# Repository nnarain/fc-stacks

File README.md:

# FC Stacks

Boards for drone electronics stacks

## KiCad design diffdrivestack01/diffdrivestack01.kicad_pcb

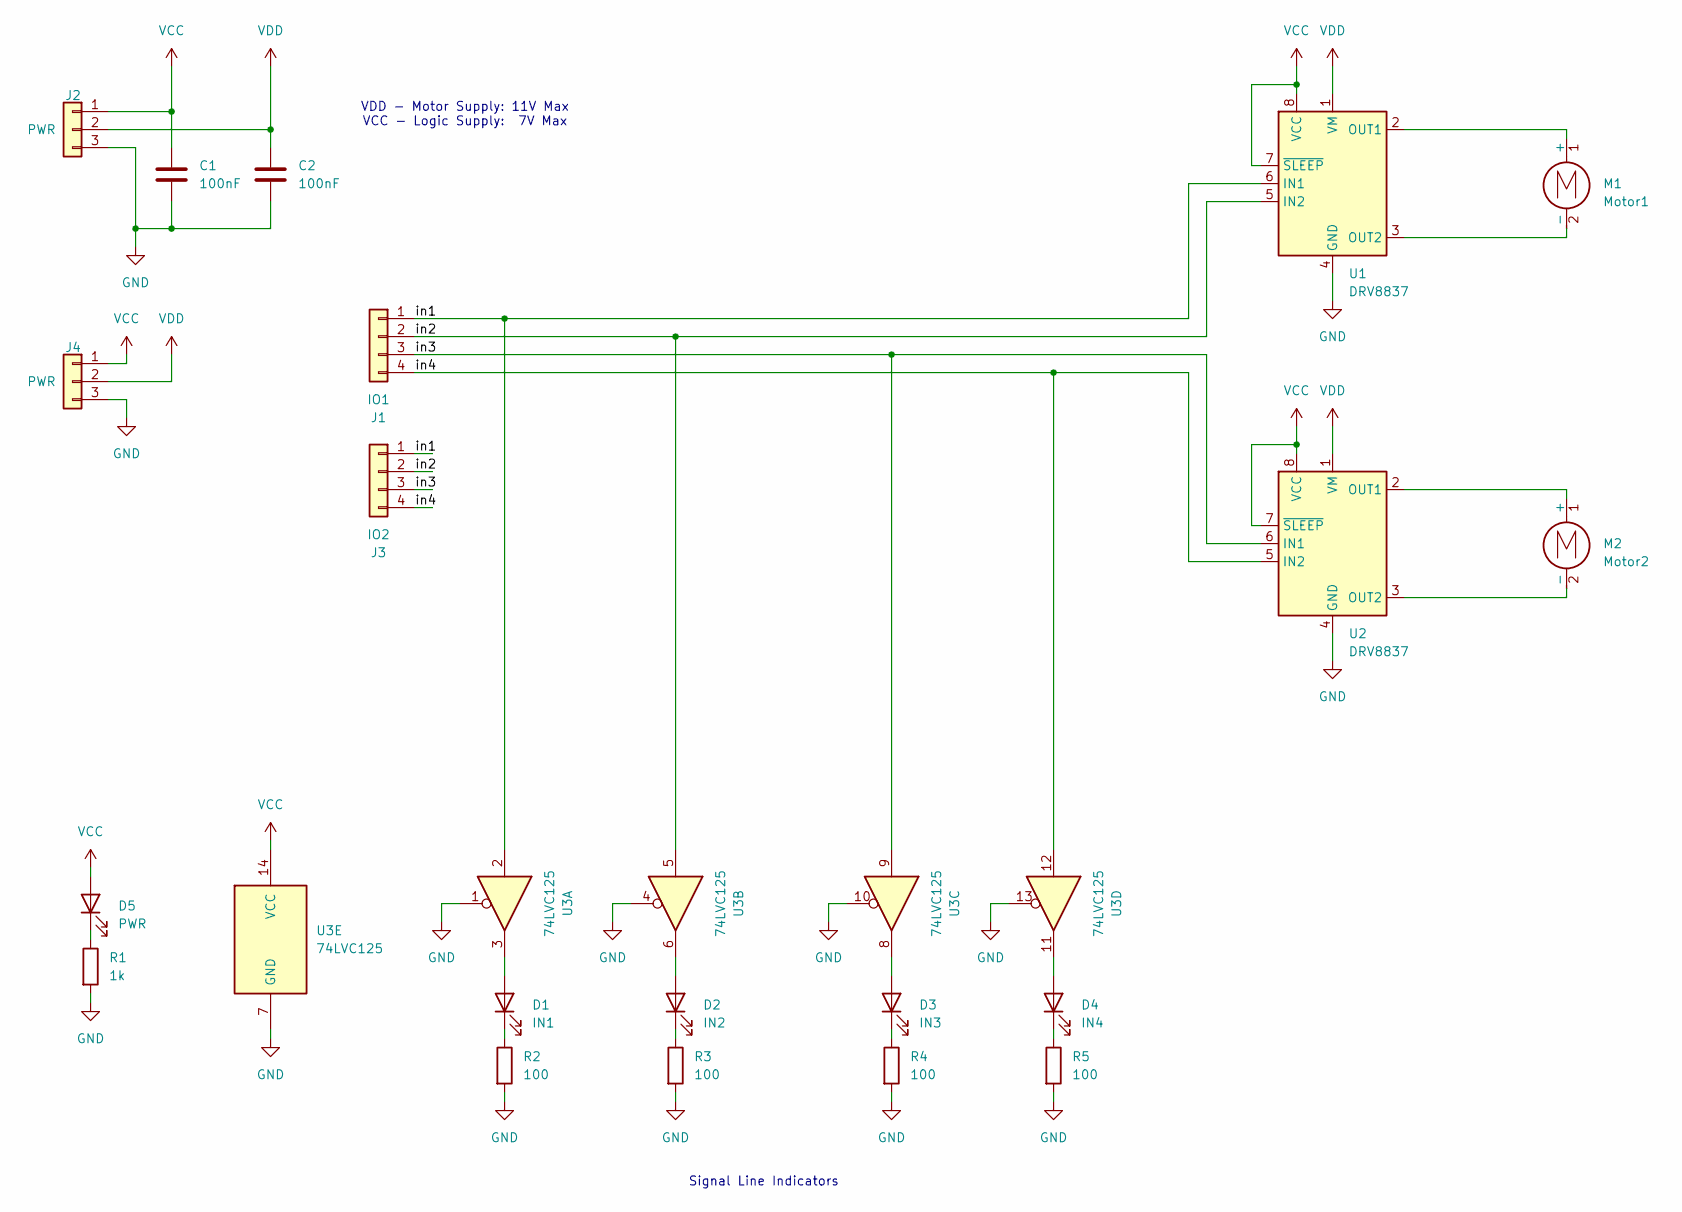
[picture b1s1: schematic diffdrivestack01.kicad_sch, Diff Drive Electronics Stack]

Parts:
C1, C2: 100nF; C_0402_1005Metric
D1: IN1; LED_0603_1608Metric; LCSC C5252984
D2: IN2; LED_0603_1608Metric; LCSC C5252984
D3: IN3; LED_0603_1608Metric; LCSC C5252984
D4: IN4; LED_0603_1608Metric; LCSC C5252984
D5: PWR; LED_0603_1608Metric; LCSC C2286
J1: IO1; SMD_4x1_1.5x1.5mm_1
J2, J4: PWR; SMD_3x1_1.5x1.5mm
J3: IO2; SMD_4x1_1.5x1.5mm_1
M1: Motor1; SMD_2x1_1.5x1.5mm
M2: Motor2; SMD_2x1_1.5x1.5mm
R1: 1k; R_0402_1005Metric; LCSC C25543
R2, R3, R4, R5: 100; R_0402_1005Metric; LCSC C25076
U1, U2: DRV8837; WSON-8-1EP_2x2mm_P0.5mm_EP0.9x1.6mm
U3: 74LVC125; TSSOP-14_4.4x5mm_P0.65mm; LCSC C6059

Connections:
/in1: J1.1, J3.1, U1.6 (IN1), U3.2
/in2: J1.2, J3.2, U1.5 (IN2), U3.5
/in3: J1.3, J3.3, U2.6 (IN1), U3.9
/in4: J1.4, J3.4, U2.5 (IN2), U3.12
GND: C1.2, C2.2, J2.3, J4.3, R1.2, R2.2, R3.2, R4.2, R5.2, U1.4 (GND), U1.9 (GND), U2.4 (GND), U2.9 (GND), U3.1, U3.4, U3.7 (GND), U3.10, U3.13
unnamed: D1.2 (A), U3.3
unnamed: D1.1 (K), R2.1
unnamed: D2.2 (A), U3.6
unnamed: D2.1 (K), R3.1
unnamed: D3.2 (A), U3.8
unnamed: D3.1 (K), R4.1
unnamed: D4.2 (A), U3.11
unnamed: D4.1 (K), R5.1
unnamed: D5.1 (K), R1.1
unnamed: M1.1 (+), U1.2 (OUT1)
unnamed: M1.2 (-), U1.3 (OUT2)
unnamed: M2.1 (+), U2.2 (OUT1)
unnamed: M2.2 (-), U2.3 (OUT2)
VCC: C1.1, D5.2 (A), J2.1, J4.1, U1.7 (~SLEEP), U1.8 (VCC), U2.7 (~SLEEP), U2.8 (VCC), U3.14 (VCC)
VDD: C2.1, J2.2, J4.2, U1.1 (VM), U2.1 (VM)

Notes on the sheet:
VDD - Motor Supply: 11V Max VCC - Logic Supply: 7V Max
Signal Line Indicators

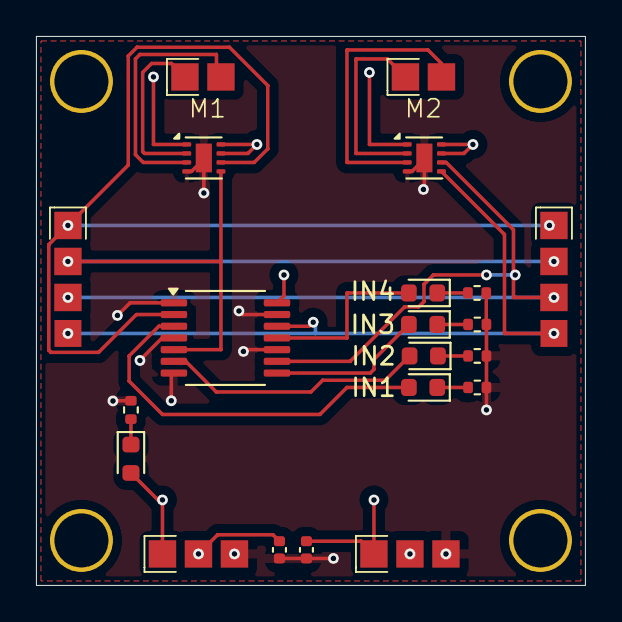
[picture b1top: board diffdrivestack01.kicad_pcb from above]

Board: 4 copper layers, 30.5 x 30.5 mm, 21 parts (0 on the bottom side), 20 nets.

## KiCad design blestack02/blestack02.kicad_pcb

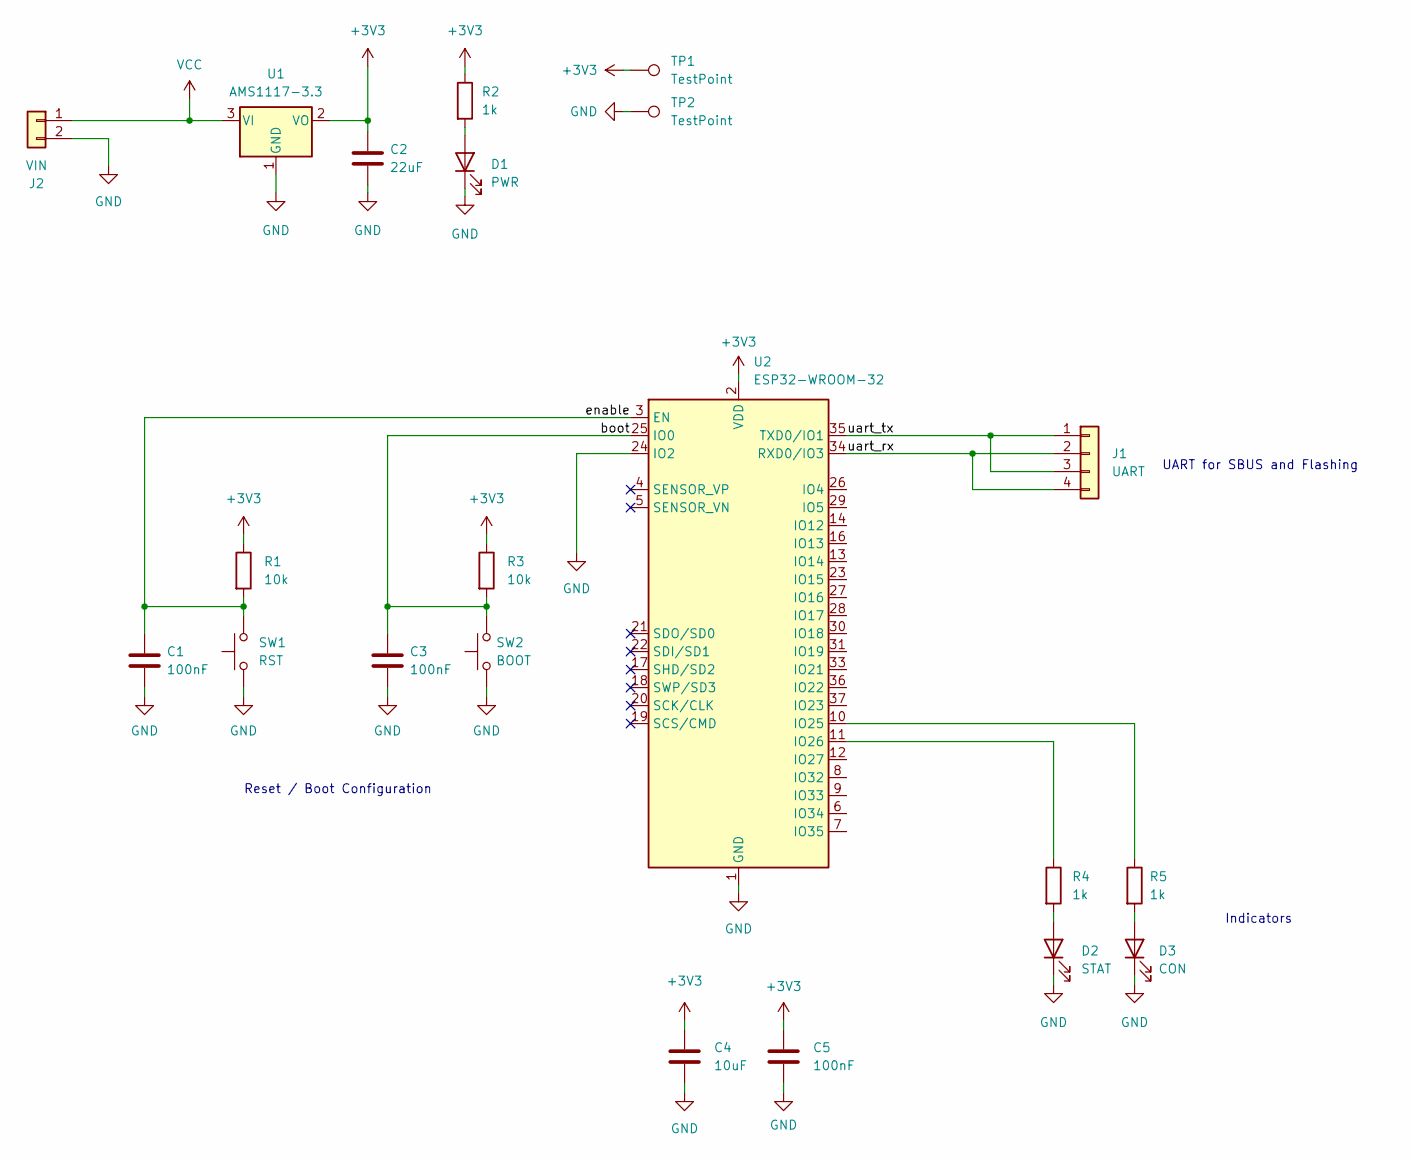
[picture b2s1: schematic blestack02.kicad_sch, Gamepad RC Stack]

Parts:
C1, C3, C5: 100nF; C_0402_1005Metric; LCSC C307331
C2: 22uF; CP_EIA-3216-18_Kemet-A; LCSC C116575
C4: 10uF; C_0402_1005Metric; LCSC C15525
D1: PWR; LED_0603_1608Metric; LCSC C2286
D2: STAT; LED_0603_1608Metric; LCSC C72043
D3: CON; LED_0603_1608Metric; LCSC C72041
J1: UART; PinHeader_1x04_P2.54mm_Vertical
J2: VIN; PinHeader_1x02_P2.54mm_Vertical
R1, R3: 10k; R_0402_1005Metric; LCSC C25744
R2, R4, R5: 1k; R_0402_1005Metric; LCSC C25543
SW1: RST; TS-1088-AR02016; LCSC C720477
SW2: BOOT; TS-1088-AR02016; LCSC C720477
TP1, TP2: TestPoint; TestPoint_Pad_1.0x1.0mm
U1: AMS1117-3.3; SOT-223-3_TabPin2; LCSC C6186
U2: ESP32-WROOM-32; LCSC C82899

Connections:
+3V3: C2.1, C4.1, C5.1, R1.1, R2.1, R3.1, TP1.1, U1.2 (VO), U2.2 (VDD)
/boot: C3.1, R3.2, SW2.2, U2.25 (IO0)
/enable: C1.1, R1.2, SW1.2, U2.3 (EN)
/uart_rx: J1.2, J1.4, U2.34 (RXD0/IO3)
/uart_tx: J1.1, J1.3, U2.35 (TXD0/IO1)
GND: C1.2, C2.2, C3.2, C4.2, C5.2, D1.1 (K), D2.1 (K), D3.1 (K), J2.2, SW1.1, SW2.1, TP2.1, U1.1 (GND), U2.1 (GND), U2.15 (GND), U2.24 (IO2), U2.38 (GND), U2.39 (GND)
unnamed: D1.2 (A), R2.2
unnamed: D2.2 (A), R4.2
unnamed: D3.2 (A), R5.2
unnamed: R5.1, U2.10 (IO25)
unnamed: R4.1, U2.11 (IO26)
VCC: J2.1, U1.3 (VI)

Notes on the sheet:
UART for SBUS and Flashing
Indicators
Reset / Boot Configuration

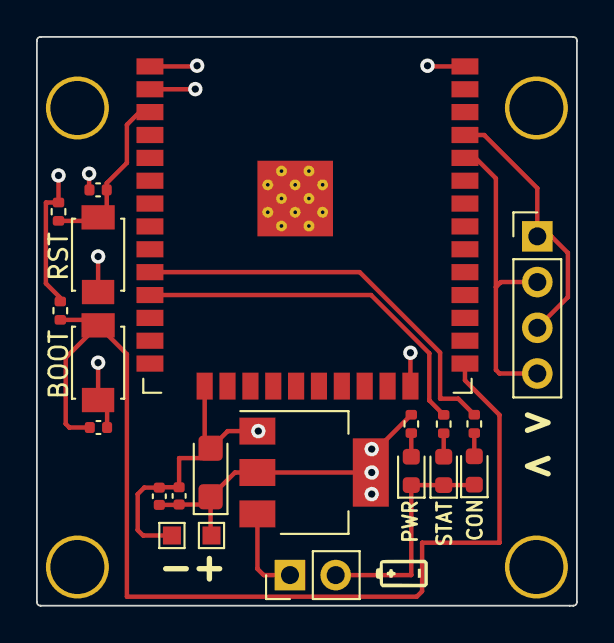
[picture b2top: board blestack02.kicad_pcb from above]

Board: 4 copper layers, 30.0 x 31.6 mm, 21 parts (0 on the bottom side), 12 nets.

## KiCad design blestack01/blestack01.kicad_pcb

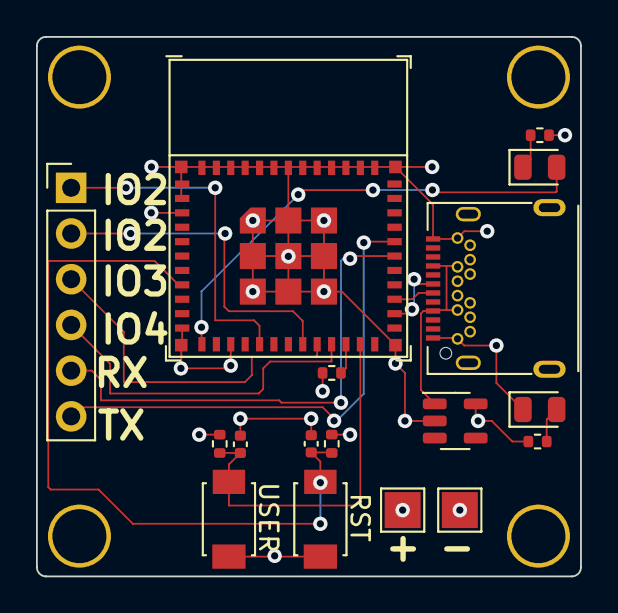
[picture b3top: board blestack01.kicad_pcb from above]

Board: 4 copper layers, 30.2 x 30.0 mm, 17 parts (0 on the bottom side), 17 nets.

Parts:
C1, C2: 100nF; C_0402_1005Metric
D1: LED; LED_0805_2012Metric
D2: PWR; LED_0805_2012Metric
J1: IO; PinHeader_1x06_P2.54mm_Vertical
P1: USB_C_Plug_USB2.0; TYPE-C-31-M-04
R1, R5: 1k; R_0402_1005Metric
R2, R3, R4: 10k; R_0402_1005Metric
SW1: USER; TS-1088-AR02016
SW2: RST; TS-1088-AR02016
TP1: TP_3V3; TestPoint_Pad_2.0x2.0mm
TP2: TP_GND; TestPoint_Pad_2.0x2.0mm
U1: AP2112K-3.3; SOT-23-5
U2: ESP32-C3-MINI-1

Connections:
+3V3: R1.1, R2.1, R3.1, R4.1, TP1.1, U1.5 (VOUT), U2.3 (3V3)
/usb_dm: P1.A7 (D-), U2.26 (GPIO18/USB_D-)
/usb_dp: P1.A6 (D+), U2.27 (GPIO19/USB_D+)
GND: C1.2, C2.2, D2.1 (K), P1.A1 (GND), P1.A12 (GND), P1.B1 (GND), P1.B12 (GND), R5.2, SW1.2, SW2.2, TP2.1, U1.2 (GND), U2.1 (GND), U2.2 (GND), U2.11 (GND), U2.14 (GND), U2.36 (GND)
unnamed: C1.1, R3.2, SW2.1, U2.8 (EN/CHIP_PU)
unnamed: C2.1, R4.2, SW1.1, U2.23 (GPIO9)
unnamed: D1.1 (K), R5.1
unnamed: D1.2 (A), U2.12 (GPIO0/ADC1_CH0/XTAL_32K_P)
unnamed: D2.2 (A), R1.2
unnamed: J1.1, U2.16 (GPIO10)
unnamed: J1.2, U2.19 (GPIO5/ADC2_CH0)
unnamed: J1.3, U2.20 (GPIO6)
unnamed: J1.4, U2.21 (GPIO7)
unnamed: J1.5, U2.30 (GPIO20/U0RXD)
unnamed: J1.6, U2.31 (GPIO21/U0TXD)
unnamed: R2.2, U2.22 (GPIO8)
VBUS: P1.A4 (VBUS), P1.A9 (VBUS), P1.B4 (VBUS), P1.B9 (VBUS), U1.1 (VIN)

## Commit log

2023-03-27 ESP32-C3 FC Stack
2023-10-15 Gamepad Stack
2024-08-05 kicad update
2024-08-10 [blestack02] Update pins for stat and con leds
2024-08-10 added python build script
2024-08-10 update LED JLCPCB part number
2024-11-08 diff drive stack
